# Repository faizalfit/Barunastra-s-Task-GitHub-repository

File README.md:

| Nama  | Division        | Sub-Division  |
| ----- | ---------- | ---------- |
| Faizal Fitrohni   | ELC | Microcontroller |

# Electrical Task 3 Submission PCB Revisions
## Schematics Design
Ini adalah gambar desain schematic untuk boost converter dengan menggunakan IC LM2577.

- Di sini saya __menggunakan typical application__ yang ada pada datasheet LM2577. 
- Pada desain boost converter ini saya juga __menggunakan dioda 1N5821__.
- Saya juga __menggunakan potensiometer (RV1)__ untuk mengatur rasio tegangan output dengan tegangan input.

Berikut adalah footprint yang saya gunakan

## PCB Design
Ini adalah gambar desain pcb boost converter saya.

- Saya __menggunakan ground plane__ pada layer back (warna biru) untuk mengurangi _Electromagnetic Interference_ (EMI) yang disebabkan oleh routing ground.
- Saya menggunakan __track dengan lebar 0.7mm__ untuk mengakomodasi power yang tinggi.
- Saya juga menggunakan vias dengan __via diameter 0,8mm__ dan __via hole 0,5mm__ yang menghubungkan komponen SMD dengan ground plane.
- Di sini saya mengusahakan agar induktor dekat dengan IC LM2577 agar loop yang terbentuk kecil. Selain itu, resistor feedback saya jauhkan dengan induktor agar _Electromagnetic Interference_ induktor tidak mengganggu resistor.

Berikut adalah hasil DRC PCB saya

## 3D Model
Berikut adalah 3d Model PCB boost converter saya

# Electrical Task 1 Submission ERC FERC Diagrams

## Electrical Diagram

## Communication Diagram

### 1. Battery (12V)
Sebagai sumber daya utama yang menyediakan listrik untuk seluruh sistem.
### 2. Fuse:
Sebagai pelindung rangkaian dari arus berlebih.

### 3. Power Distribution Board:
1. ___LED___: Indikator visual untuk menunjukkan status daya.
2. ___Voltage Regulator___: Menstabilkan tegangan untuk menghindari fluktuasi yang dapat merusak komponen.
3. ___Buck (5V)___: Mengubah tegangan 12V menjadi 5V untuk komponen yang memerlukan daya lebih rendah.
4. ___ESC (Electronic Speed Controller)___: Mengatur kecepatan dan arah motor.
5. ___Motor___: Menghasilkan gerakan atau daya dorong.

### 4. Microcontroller Board:
1. ___STM32H7___: pengontrol utama untuk memproses data dan memberikan sinyal kendali ke seluruh sistem.
2. ___Relay___: Mengontrol aliran daya ke  pendingin dan fuel system board.
3. ___Servo___: Mengontrol arah gerak kapal 
4. ___Receiver dan Transmitter___: Menerima dan mengirim sinyal pengendali jarak jauh.

### 5. Fuel System Board:
Komponen Utama:
1. ___LED___: Indikator status untuk sistem bahan bakar.
2. ___Fuel Level Sensor___: Mengukur tingkat bahan bakar dalam tangki.
3. ___Fuel Pump___: Memompa bahan bakar ke sistem pembakaran atau mekanisme terkait.
4. ___Buck (12V)___: Menstabilkan tegangan ke komponen sistem bahan bakar.

### 6. Cooling System:
Mengatur suhu sistem agar tetap dalam batas aman.

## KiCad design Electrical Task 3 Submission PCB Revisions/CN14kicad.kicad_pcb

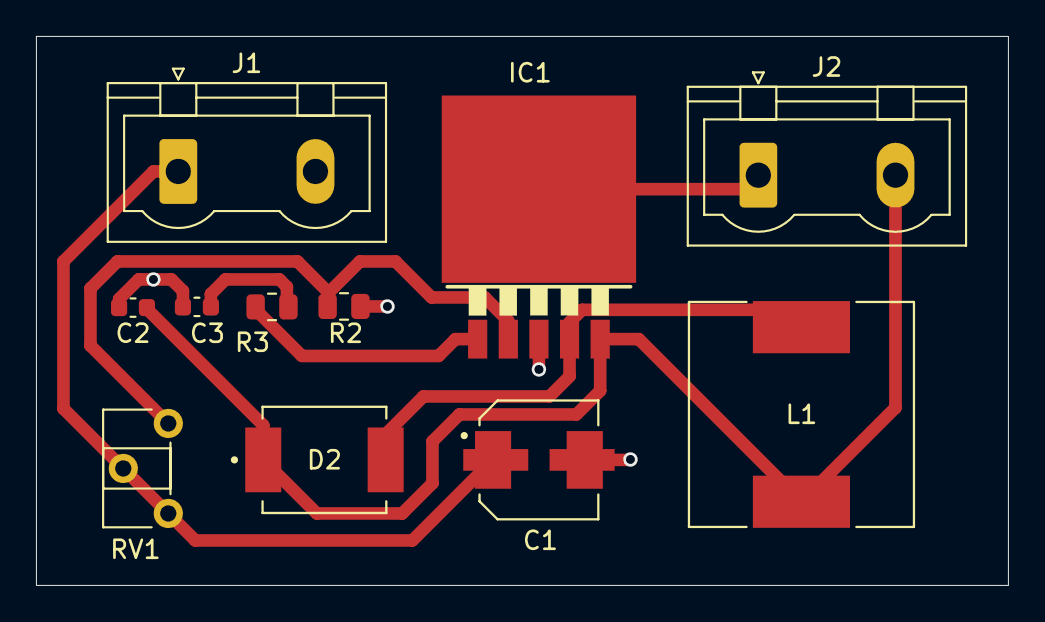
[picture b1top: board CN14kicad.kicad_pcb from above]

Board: 2 copper layers, 54.0 x 30.5 mm, 11 parts (0 on the bottom side), 7 nets.

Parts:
C1: 680u; CAP_EEEFK1C101V
C2: 0.1u; C_0603_1608Metric
C3: 0.33u; C_0603_1608Metric
D2: 1N5821; DIO_SS34
IC1: LM2577; TO263-5
J1, J2: Conn_01x02_Socket; PhoenixContact_GMSTBVA_2,5_2-G-7,62_1x02_P7.62mm_Vertical
L1: 100uH; INDP125125X600N
R2: 2k; R_0805_2012Metric
R3: 2.2k; R_0805_2012Metric
RV1: 50k; Potentiometer_ACP_CA6-H2,5_Horizontal

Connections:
+5V: C2.1, D2.C, IC1.5 (VIN), J2.2, L1.1
+12V: C1.1, J1.1, RV1.1, RV1.2
GND: C1.2, C2.2, C3.2, IC1.3 (GND), IC1.6, J1.2, J2.1, R2.2
unnamed: C3.1, R3.2
unnamed: D2.A, IC1.4 (VSW), L1.2
unnamed: IC1.1 (COMP), R3.1
unnamed: IC1.2 (FB), R2.1, RV1.3

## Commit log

2024-11-23 Added Image, Draw.io files, and explanations
2024-11-23 fixing images
2024-11-23 image fixed
2024-11-23 images fixed
2024-11-23 add images
2024-11-27 Tugas 2
2024-11-27 Penjelasan Operator If Func
2024-11-29 ERC and FERC
2024-11-29 KiCad Schematic and PCB Design
2024-11-29 add more images
2024-11-29 update the explanation
2024-11-30 C Languange Task
